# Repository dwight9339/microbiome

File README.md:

# microbiome

An embedded ecosystem: a small, mostly-ambient world drawn on a little screen,
where animals wander in and out according to time of day, season, weather and
chance, and react to each other. You pan around it with arrow buttons; when you
stop, the camera slowly and occasionally drifts toward whatever is interesting.

The engine knows nothing about forests or deer. Everything in a scene (art,
layers, animals, their behaviour, spawn rules, lighting, weather) is
declarative data in a **pack** (`packs/<name>/pack.yaml` + PNGs), compiled
to a compact binary blob that the engine reads in place from flash.

```
 packs/forest/pack.yaml ─┐
 packs/forest/art/*.png ─┴─ packc ──> forest.mbp ──> engine core (C11, no heap)
                                                       ├─ platform/sdl       desktop simulator
                                                       ├─ platform/headless  PNG snapshots / tests
                                                       ├─ platform/wasm      browser viewer, future studio
                                                       └─ platform/rp2350    Pico 2 + ST7789/ILI9341 firmware
```

## Quick start (desktop)

You need CMake ≥ 3.16, a C compiler, Python 3 with PyYAML and Pillow, and
SDL2 for the simulator. Without SDL2 everything else still builds; CMake
just skips `mbsim`.

### Ubuntu / Debian

```sh
sudo apt install build-essential cmake libsdl2-dev python3-yaml python3-pil
cmake -B build && cmake --build build
./build/mbsim build/forest.mbp                 # 320x240 at 3x zoom
./build/mbsim build/forest.mbp --size 480x480
ctest --test-dir build
```

(On Ubuntu 23.04+ a bare `pip install` is refused, so use the apt packages
above, or a venv: `python3 -m venv .venv && .venv/bin/pip install pyyaml pillow`,
then configure with `-DPython3_EXECUTABLE=$PWD/.venv/bin/python`.)

### macOS

```sh
brew install cmake sdl2 && pip3 install pyyaml pillow
cmake -B build && cmake --build build && ./build/mbsim build/forest.mbp
```

### Windows (Visual Studio 2022)

1. Install **Visual Studio 2022** with "Desktop development with C++" (it includes CMake),
   and **Python 3** from python.org (tick "Add to PATH"). Then `pip install pyyaml pillow`.
2. Download `SDL2-devel-2.30.x-VC.zip` from the
   [SDL releases page](https://github.com/libsdl-org/SDL/releases) (**SDL2**, not SDL3) and unzip it,
   e.g. to `C:\libs\SDL2-2.30.9`.
3. From a *Developer PowerShell for VS 2022* in the repository:

```powershell
cmake -B build -DSDL2_DIR=C:\libs\SDL2-2.30.9\cmake
cmake --build build --config Release
.\build\Release\mbsim.exe build\forest.mbp
ctest --test-dir build -C Release
```

The build copies `SDL2.dll` next to `mbsim.exe` automatically. vcpkg works too:
`vcpkg install sdl2:x64-windows`, then configure with
`-DCMAKE_TOOLCHAIN_FILE=<vcpkg>\scripts\buildsystems\vcpkg.cmake` instead of `SDL2_DIR`.

**Alternatively, use WSL2.** On Windows 11, Linux GUI apps display natively,
so the Ubuntu steps above work unchanged inside WSL, simulator window included.

CI (`.github/workflows/ci.yml`) builds and tests on Ubuntu and Windows, runs a
sanitizer soak test, and builds the firmware.

| Key | Action |
| --- | --- |
| arrows | pan |
| Z / X | A / B buttons (not used by the forest pack yet) |
| T | time speed 1× → 60× → 600× |
| `[` / `]` | hour −/+ |
| W | cycle weather (pinned) → back to automatic |
| D (or F1) | debug overlay: actor boxes, places, lanes, obstacles, occluder bases; states in title bar |
| R | reload pack |

**Iterating on content.** Run the compiler in watch mode next to the
simulator. Every save of `pack.yaml` or a PNG rebuilds the pack, and `mbsim`
hot-reloads it, keeping camera and time:

```sh
python3 tools/packc/packc.py packs/forest -o build/forest.mbp --watch
```

**Snapshots without a display** (art review, CI, agents):

```sh
./build/mbsnap build/forest.mbp night.png --time 22:30 --set weather=clear --sim 120
./build/mbsnap build/forest.mbp pano.png --panorama          # whole world, unscrolled
./build/mbsnap build/forest.mbp shot.png --frames 20 --every 100   # animation strip
./build/mbsnap build/forest.mbp - --info --sim 600            # vars, actors, spawn-rule status
```

`ctest --test-dir build` runs smoke tests. With `pip install jsonschema` it
also checks `pack.yaml` against the [pack schema](docs/pack-format.md#editor-support).

## In a browser (WebAssembly)

The same engine core, compiled to WebAssembly with plain clang (no Emscripten),
with a small viewer: time scrubbing, pinned variables, a debug overlay,
click-to-inspect, and spawn-rule status. Drop a `.mbp` on it to load another pack.

```sh
sudo apt install clang lld nodejs        # macOS: brew install llvm lld node
cmake -S platform/wasm -B build-wasm && cmake --build build-wasm
ctest --test-dir build-wasm              # add -DMB_MBSNAP=build/mbsnap when configuring for the pixel-parity test
python3 -m http.server -d build-wasm/web 8000   # open http://localhost:8000
```

CI uploads a ready-built `microbiome-web` artifact, so you can also just serve
that folder. `build-wasm/web/microbiome.js` is the JS API (typed in
`microbiome.d.ts`) that the planned [studio](docs/studio.md) builds on.

## Firmware (RP2350 / Pico 2)

**No toolchain needed to try it:** every CI run uploads a `microbiome-firmware`
artifact (Actions tab → a run → Artifacts) containing `.uf2` builds with and
without RTC support. Hold BOOTSEL, plug in the Pico 2, and copy the `.uf2` to the drive.

To build it yourself on Ubuntu (or WSL):

```sh
sudo apt install gcc-arm-none-eabi libnewlib-arm-none-eabi libstdc++-arm-none-eabi-newlib
git clone -b 2.1.1 https://github.com/raspberrypi/pico-sdk && (cd pico-sdk && git submodule update --init lib/tinyusb)
export PICO_SDK_PATH=$PWD/pico-sdk
cmake -S platform/rp2350 -B build-rp2350          # add -DMB_RTC_DS3231=ON if you fit an RTC
cmake --build build-rp2350
```

On native Windows, Raspberry Pi's VS Code "Raspberry Pi Pico" extension
installs the SDK and toolchain. Point it at `platform/rp2350` (not tested yet;
WSL and CI are the known-good paths).

Default wiring for a 2.0" 240×320 ST7789V module (all pins in
`platform/rp2350/board_config.h`):

| LCD pin | Pico 2 | | Button | Pico 2 |
| --- | --- | --- | --- | --- |
| VCC | 3V3 (36) | | left | GP2 |
| GND | GND | | right | GP3 |
| SCL | GP18 | | up | GP4 |
| SDA | GP19 | | down | GP5 |
| RES | GP20 | | A | GP6 |
| DC | GP16 | | B | GP7 |
| CS | GP17 | | | (buttons to GND) |
| BLK | GP21 | | | |

If the picture is mirrored, rotated or has inverted colours, change
`LCD_MADCTL` / `LCD_INVERT` in `board_config.h`.

**Other boards** go in a small header under `platform/rp2350/boards/` that
overrides only what differs, selected with `-DMB_BOARD_CONFIG=boards/<file>.h`.
`boards/ili9341_32.h` is LCDwiki's MSP3223, a 3.2" 240×320 IPS ILI9341V module.
Its CI build is `build-rp2350-ili9341/microbiome.uf2` in the firmware artifact.

| Module pin | Pico 2 | | Module pin | Pico 2 |
| --- | --- | --- | --- | --- |
| 1 VCC | VBUS (40) | | 5 RS | GP17 |
| 2 GND | GND | | 6 SDI (MOSI) | GP19 |
| 3 CS | GP21 | | 7 SCK | GP18 |
| 4 RST | GP20 | | 8 LED | GP16 |

SPI pins are fixed in silicon: on SPI0, SCK must be GP2/6/18/22 and MOSI
GP3/7/19/23, and the firmware refuses to build otherwise. CS, RS/DC, RST and
LED can be any GPIO.

The USB serial console takes `time 07:30`, `date 2026-12-25`, `speed 60`,
`set weather precip`, `stats`, and for display bring-up `fill FF0000` (hold a
solid colour) and `run` (resume).

## Repository layout

| Path | What |
| --- | --- |
| `core/` | The engine: pack loader/validator, clock & world variables, actors, particles, strip renderer. Portable C11, no allocation, no platform code. |
| `core/include/mb/pack_format.h` | The binary pack format (the contract between `packc` and the engine). |
| `tools/packc/packc.py` | Pack compiler: YAML + PNG → `.mbp`. |
| `tools/packc/pack.schema.json` | JSON Schema for `pack.yaml` (editor autocomplete, studio forms); `check_schema.py` validates against it. |
| `tools/placeholder_art.py` | Generates the current placeholder forest art. |
| `tools/palette.py` | Pack palettes (`.gpl`, opens in Aseprite): snap art onto one, preview, check. |
| `tools/sprite_from_ref.py` | Reference art (generated, painted) → palette-locked sprite frames to finish in Aseprite. See `docs/art-workflow.md`. |
| `packs/forest/` | The forest pack. |
| `packs/glade/` | The forest animals in a painted lakeside clearing (`./build/mbsim build/glade.mbp`; firmware: `-DMB_PACK=glade`). |
| `platform/sdl/` | Desktop simulator with hot reload. |
| `platform/headless/` | `mbsnap` PNG renderer. |
| `platform/wasm/` | WebAssembly host, JS API (`microbiome.js`) and web viewer. |
| `platform/rp2350/` | Pico 2 firmware: ST7789/ILI9341 DMA driver, board configs, buttons, optional DS3231, serial console. |
| `docs/architecture.md` | How the engine works and how to port it. |
| `docs/pack-format.md` | Writing packs: the YAML schema, behaviours, and art requirements. |
| `docs/art-workflow.md` | Making animal sprites: generate a reference, convert it, finish it in Aseprite. |
| `docs/studio.md` | Plan for microbiome Studio, a desktop/browser scene editor. |

## Product vision and roadmaps

Microbiome is planned as three connected products: Engine & Firmware, Studio
(world creation), and a separate Companion desktop app (devices, updates, worlds).

- [Project vision](docs/vision.md)
- [Unified three-track roadmap](docs/roadmap.md)
- [Christmas 2026 gift-first plan](docs/gift-2026.md)
- [Feather RP2350 carrier board hardware plan](docs/hardware/feather-carrier-2026.md)
- [Engine & Firmware roadmap](docs/roadmaps/engine-firmware.md)
- [Studio roadmap](docs/roadmaps/studio.md)
- [Companion roadmap](docs/roadmaps/companion.md)
- [Ideas and discovery backlog](docs/ideas.md)

The immediate target is **Friday, December 18, 2026**: gift-ready devices on a
custom PCB and enclosure, running one new world on reliable firmware, with a
basic Studio to help lay the world out. The docs are drafts.

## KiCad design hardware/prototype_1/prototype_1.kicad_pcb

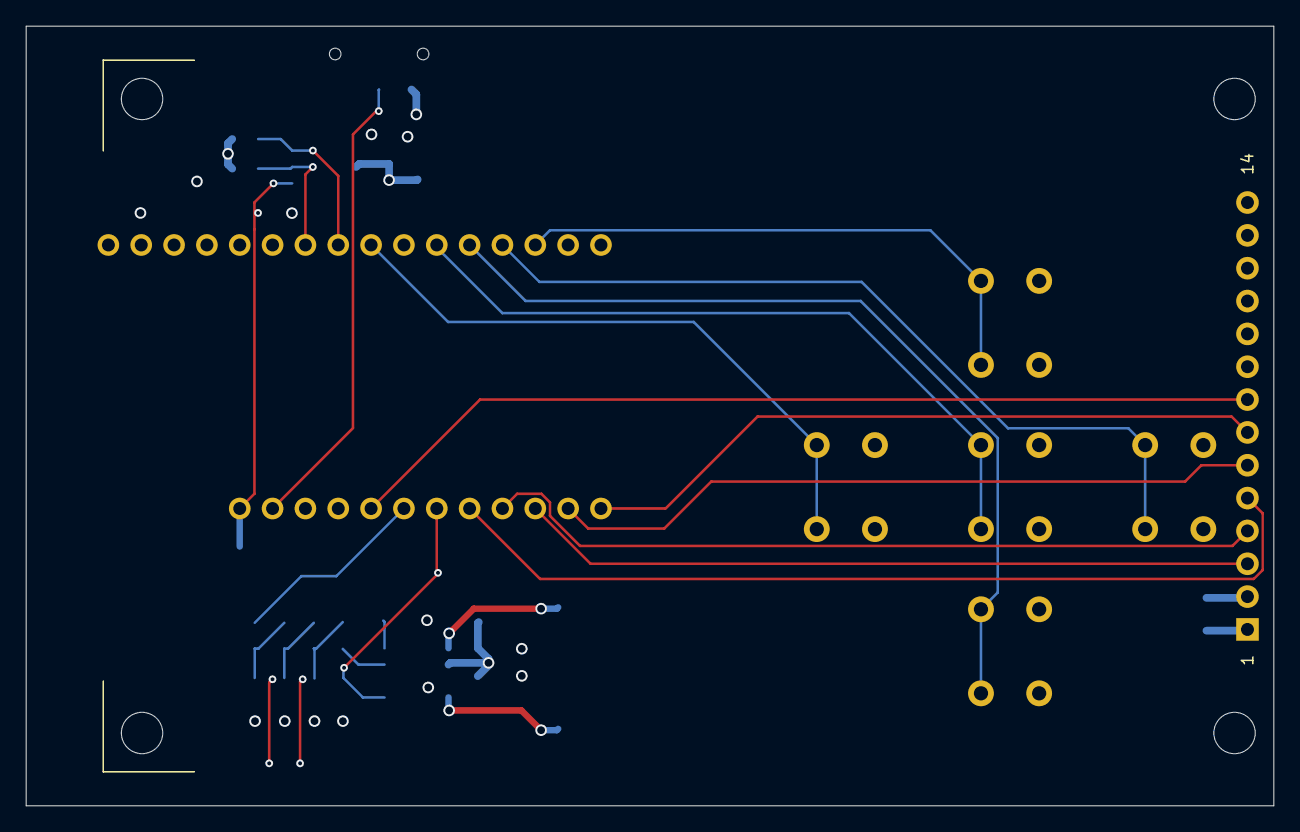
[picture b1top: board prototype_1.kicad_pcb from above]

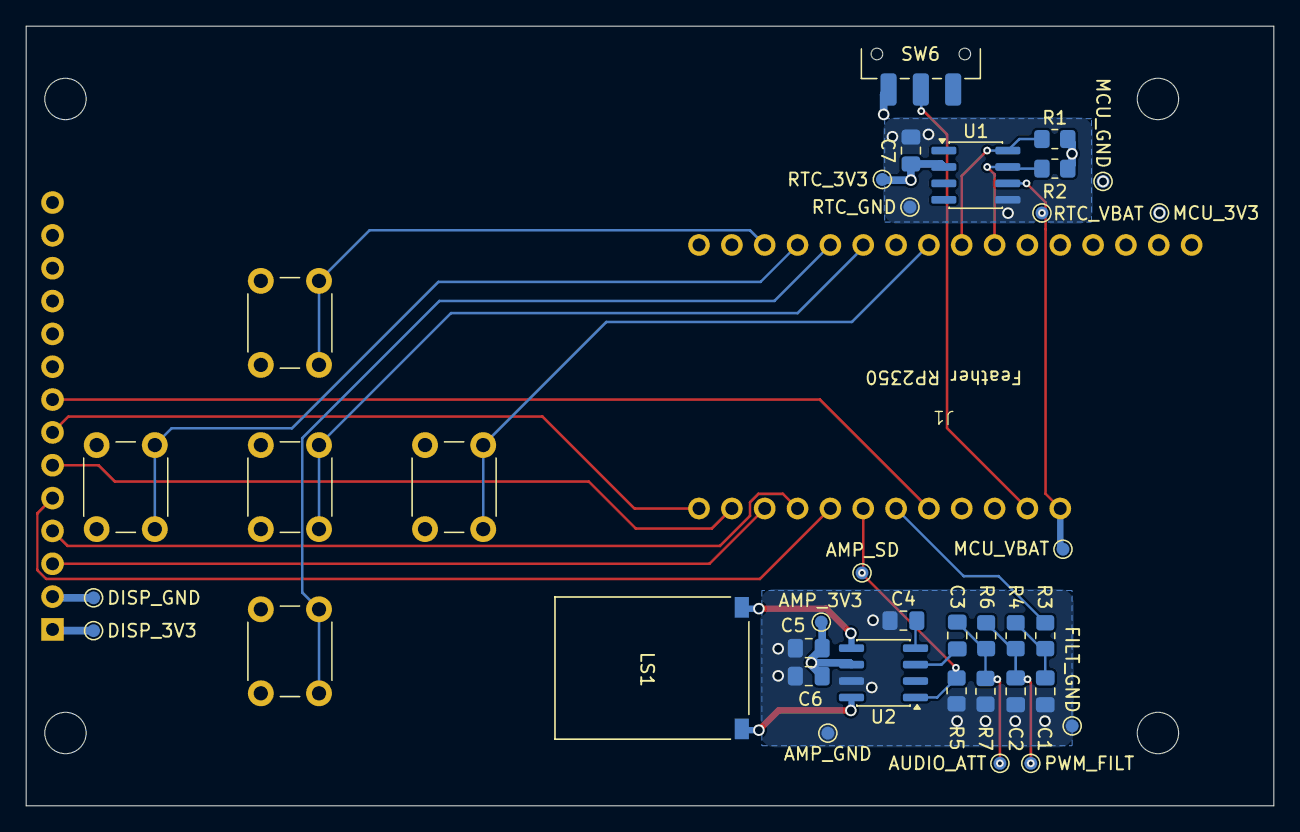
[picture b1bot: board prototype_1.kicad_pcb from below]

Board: 4 copper layers, 96.5 x 60.3 mm, 39 parts (38 on the bottom side), 26 nets.

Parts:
C1, C2: 10nF; C_0805_2012Metric_Pad1.18x1.45mm_HandSolder
C3, C4: 220nF; C_0805_2012Metric_Pad1.18x1.45mm_HandSolder
C5: 10uF; C_0805_2012Metric_Pad1.18x1.45mm_HandSolder
C6: 1uF; C_0805_2012Metric_Pad1.18x1.45mm_HandSolder
C7: 100nF; C_0805_2012Metric_Pad1.18x1.45mm_HandSolder
J1: Feather RP2350; Adafruit_Feather_RP2350
J2: MSP3223_3.2in_IPS_SPI
LS1: Speaker; SPKR_AS01508AO-SC-WP-R
R1, R2: 4.7k; R_0805_2012Metric_Pad1.20x1.40mm_HandSolder
R3, R4: 1k; R_0805_2012Metric_Pad1.20x1.40mm_HandSolder
R5: 100k; R_0805_2012Metric_Pad1.20x1.40mm_HandSolder
R6, R7: 10k; R_0805_2012Metric_Pad1.20x1.40mm_HandSolder
SW1, SW2, SW3, SW4, SW5: SW_Push; SW_PUSH_6mm_H7.3mm
SW6: SW_SPDT; SW_SPDT_CK_JS102011SAQN
TP1: MCU_3V3; TestPoint_Pad_D1.0mm
TP2: MCU_VBAT; TestPoint_Pad_D1.0mm
TP3: MCU_GND; TestPoint_Pad_D1.0mm
TP4: DISP_3V3; TestPoint_Pad_D1.0mm
TP5: DISP_GND; TestPoint_Pad_D1.0mm
TP6: PWM_FILT; TestPoint_Pad_D1.0mm
TP7: FILT_GND; TestPoint_Pad_D1.0mm
TP8: AMP_3V3; TestPoint_Pad_D1.0mm
TP9: AMP_SD; TestPoint_Pad_D1.0mm
TP10: AMP_GND; TestPoint_Pad_D1.0mm
TP11: RTC_3V3; TestPoint_Pad_D1.0mm
TP12: RTC_VBAT; TestPoint_Pad_D1.0mm
TP13: RTC_GND; TestPoint_Pad_D1.0mm
TP14: AUDIO_ATT; TestPoint_Pad_D1.0mm
U1: DS3231MZ; SOIC-8_3.9x4.9mm_P1.27mm
U2: PAM8302AAD; SOIC-8_3.9x4.9mm_P1.27mm

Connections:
/3V3: C5.2, C6.2, C7.2, J1.3V3, J2.1 (VCC), R1.2, R2.2, TP1.1 (1_1), TP4.1 (1_1), TP8.1 (1_1), TP11.1 (1_1), U1.2 (VCC), U2.6 (VDD)
/AMP_SD: J1.GP10, R5.2, TP9.1 (1_1), U2.1 (~SD)
/AUDIO_PWM_FILT: C3.2, U2.3 (IN+)
/AUDIO_PWM_RAW: J1.GP11, R3.1
/BTN_CENTER: J1.GP22, SW5.1
/BTN_DOWN: J1.GP23, SW2.1
/BTN_LEFT: J1.GP24, SW3.1
/BTN_RIGHT: J1.GP20, SW4.1
/BTN_UP: J1.GP1, SW1.1
/I2C_SCL: J1.GP29, R1.1, U1.8 (SCL)
/I2C_SDA: J1.GP28, R2.1, U1.7 (SDA)
/MCU_EN: J1.EN, SW6.2 (B)
/TFT_BL: J1.GP4, J2.8 (LED)
/TFT_CS: J1.GP5, J2.3 (LCD_CS)
/TFT_DC: J1.GP9, J2.5 (LCD_RS)
/TFT_MOSI: J1.GP3, J2.6 (SDI(MOSI))
/TFT_RST: J1.GP6, J2.4 (LCD_RST)
/TFT_SCK: J1.GP2, J2.7 (SCK)
/VBAT: J1.VBAT, TP2.1 (1_1), TP12.1 (1_1), U1.6 (VBAT)
GND: C1.2, C2.2, C4.1, C5.1, C6.1, C7.1, J1.GND, J2.2 (GND), R5.1, R7.1, SW1.2, SW2.2, SW3.2, SW4.2, SW5.2, SW6.3 (C), TP3.1 (1_1), TP5.1 (1_1), TP7.1 (1_1), TP10.1 (1_1), TP13.1 (1_1), U1.5 (GND), U2.7 (GND)
unnamed: C1.1, R3.2, R4.1
unnamed: C2.1, R4.2, R6.1, TP6.1 (1_1)
unnamed: C3.1, R6.2, R7.2, TP14.1 (1_1)
unnamed: C4.2, U2.4 (IN-)
unnamed: LS1.1, U2.5 (OUT+)
unnamed: LS1.2, U2.8 (OUT-)
